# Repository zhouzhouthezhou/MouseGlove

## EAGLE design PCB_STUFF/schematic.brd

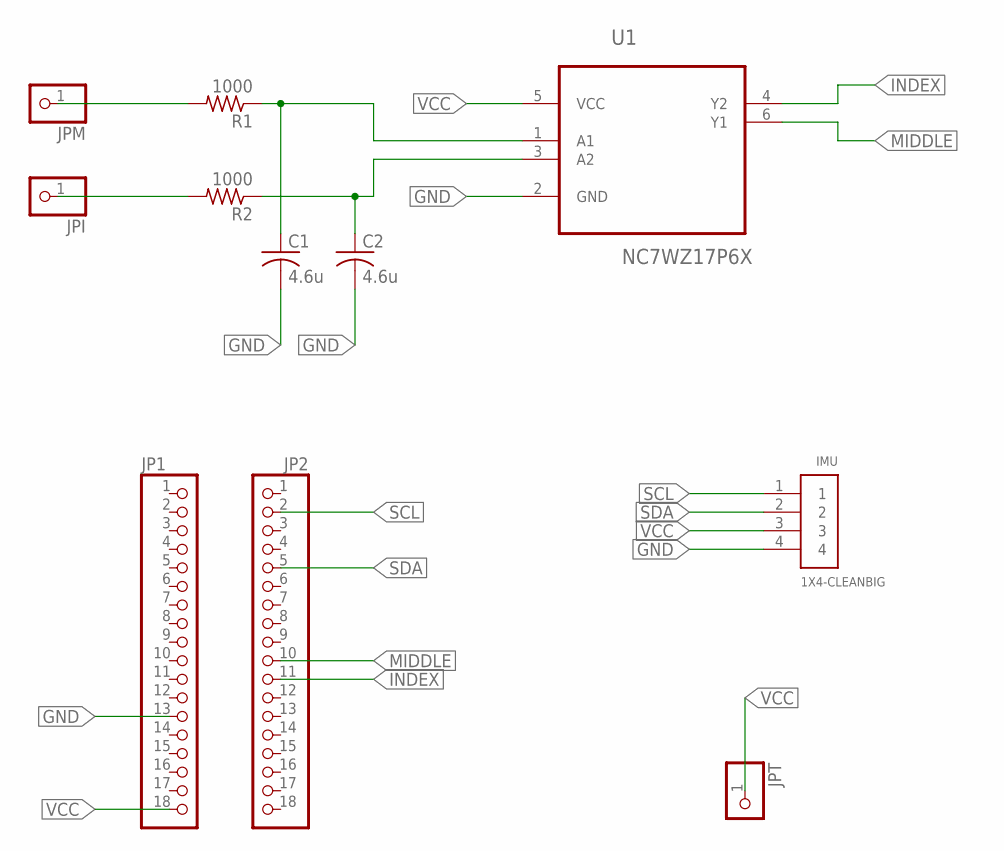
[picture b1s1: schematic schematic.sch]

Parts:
C1, C2: 4.6u; C0805
IMU: 1X4-CLEANBIG; 1X04-CLEANBIG
JP1, JP2: PINHD-1X18-BIG; 1X18-BIG
JPI: PINHD-1X1CB; 1X01-CLEANBIG
JPM: PINHD-1X1CB; 1X01-CLEANBIG
JPT: PINHD-1X1CB; 1X01-CLEANBIG
R1, R2: 1000; M0805
U1: NC7WZ17P6X; SOT65P210X110-6N

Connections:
GND: C1.2, C2.2, IMU.4, JP1.13, U1.2 (GND)
INDEX: JP2.11, U1.4 (Y2)
MIDDLE: JP2.10, U1.6 (Y1)
unnamed: C1.1, R1.1, U1.1 (A1)
unnamed: C2.1, R2.1, U1.3 (A2)
unnamed: JPM.1, R1.2
unnamed: JPI.1, R2.2
SCL: IMU.1, JP2.2
SDA: IMU.2, JP2.5
VCC: IMU.3, JP1.18, JPT.1, U1.5 (VCC)

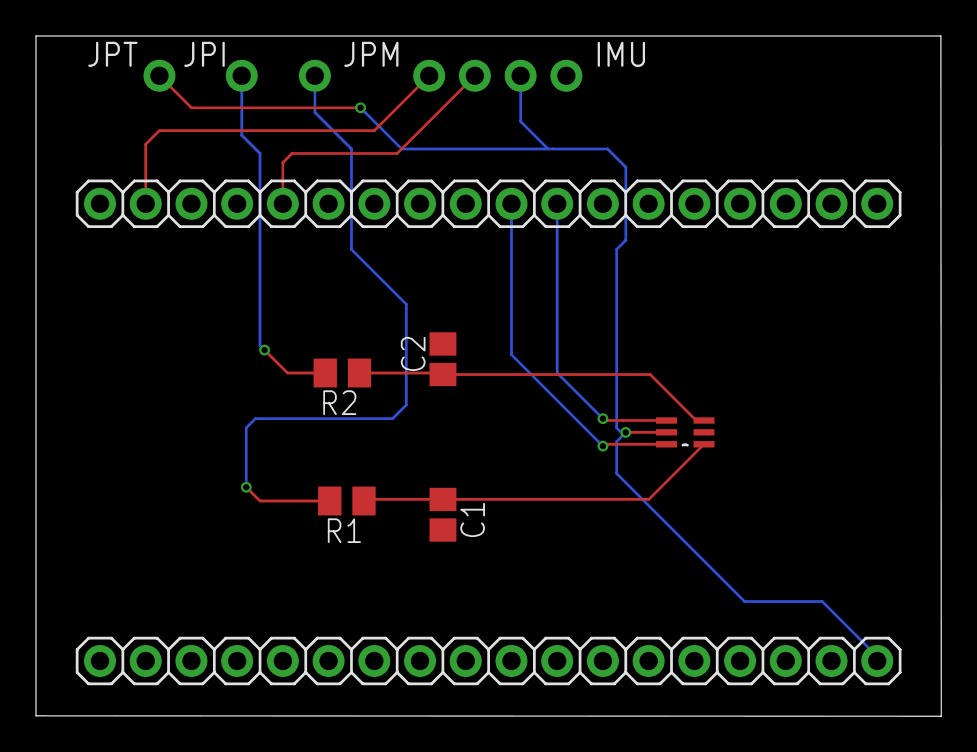
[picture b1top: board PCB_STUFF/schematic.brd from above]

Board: 2 copper layers, 50.3 x 37.8 mm, 11 parts (0 on the bottom side), 10 nets.

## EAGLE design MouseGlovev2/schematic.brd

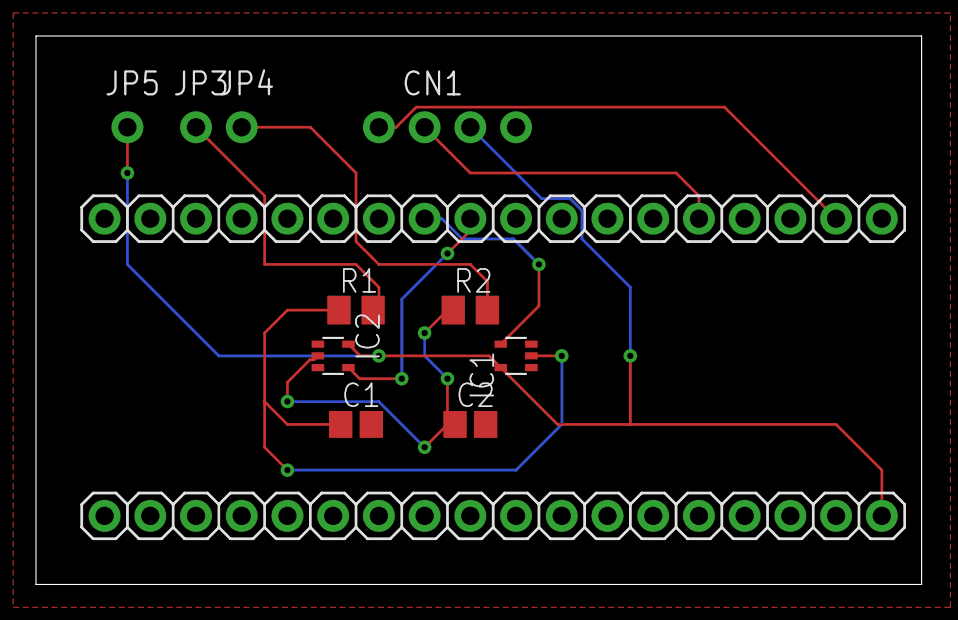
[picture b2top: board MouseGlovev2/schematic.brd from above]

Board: 2 copper layers, 49.2 x 30.5 mm, 12 parts (0 on the bottom side), 10 nets.

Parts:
C1, C2: 4.6u; C0805
CN1: 1X4-CLEANBIG; 1X04-CLEANBIG
IC1, IC2: 74AUC1G17DCK; SC70-5
JP1, JP2: 1X18-BIG
JP3, JP4, JP5: 1X01-CLEANBIG
R1, R2: 1000; M0805

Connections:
GND: C1.2, C2.2, CN1.4, IC1.3, IC2.3, JP1.13
INDEX: IC1.4, JP2.11
MIDDLE: IC2.4, JP2.10
unnamed: C1.1, IC1.2, R1.1
unnamed: C2.1, IC2.2, R2.1
unnamed: JP3.1, R1.2
unnamed: JP4.1, R2.2
SCL: CN1.1, JP2.2
SDA: CN1.2, JP2.5
VCC: CN1.3, IC1.5, IC2.5, JP1.18, JP5.1

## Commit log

2019-11-14 Added basic eagle files
    TODO: Rerout PCB
    TODO: Fix spacing on ESP rails
    TODO: Create correct footprint for Schmitt Triggers
2019-11-18 Compleated PCB design
2019-11-26 Fuck u Kyle
2019-11-30 Big glove guys
2019-11-30 3D Motion tracking algorithm
2019-11-30 hid testing
2019-12-02 added left a right click ability + interfacing with infterface pcb over wired connection
2019-12-04 added full arduino bluetooth mouse events
2019-12-06 Updated IMU code
2019-12-08 Python Code
2019-12-08 figuring out i2c for esp32
2019-12-08 Python code v.2
2019-12-08 testing bank select
2019-12-08 testing selecting different banks
2019-12-08 testing read from acceleromiter and gyro registers
2019-12-08 added imu initialization/ configuration method
2019-12-08 more test
2019-12-08 error fixing
2019-12-08 more error fixes
2019-12-08 kill me
2019-12-08 unpacking bites
2019-12-08 BIG INDIAN
2019-12-08 more testing
2019-12-08 back to unpack
2019-12-08 bbbbb
2019-12-08 bank
2019-12-08 added acceleromiter and gyroscope scaling and normalization
2019-12-08 added a silent back slect
2019-12-08 added full gyro algorithm
2019-12-08 orientaldjfsak
2019-12-08 Final orientation code
2019-12-08 test
2019-12-08 uart skelitor
2019-12-08 add uart
2019-12-09 Implemented initialization and sending of UART
2019-12-09 uart testing
2019-12-09 fdsa
2019-12-09 Debugging
2019-12-09 UART bluetooth working
2019-12-09 Wireless af
2019-12-09 fdasfds
2019-12-09 Added read_click function
2019-12-09 final expo revision
